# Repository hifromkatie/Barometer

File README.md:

Code and circuit diagrams for Wall mounted Barometer project.

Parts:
Arduino Uno Farnell: 2075382
MIKROE-1581 Arduino Uno click shield  Farnell:2431450
MIKROE-3216 Pressure 6 click Board (BM1386GLV Sensor) Farnell: 3013769
144LEDs per meter Neopixel strip  Farnell: 2816235
DS1307+ RTC Farnell: 2515369
32.768KHz Crystal  Farnell: 3264229
2032 coin cell  Farnell: 249877

Others: Strip board, Header pins (straight & right angle), molex connector housing & crip contacts and resistors (10K & 470).

Arduino-barometer_V0.2
Code for Arduino.

BM1386GLV_lib
library for BM1386GLV Barometric pressure sensor whhic is on the Pressure 6 Click board

RTC-mikroBUS
Schematic for RTC board, compatible with mikroBUS pin out for using with Click shield.

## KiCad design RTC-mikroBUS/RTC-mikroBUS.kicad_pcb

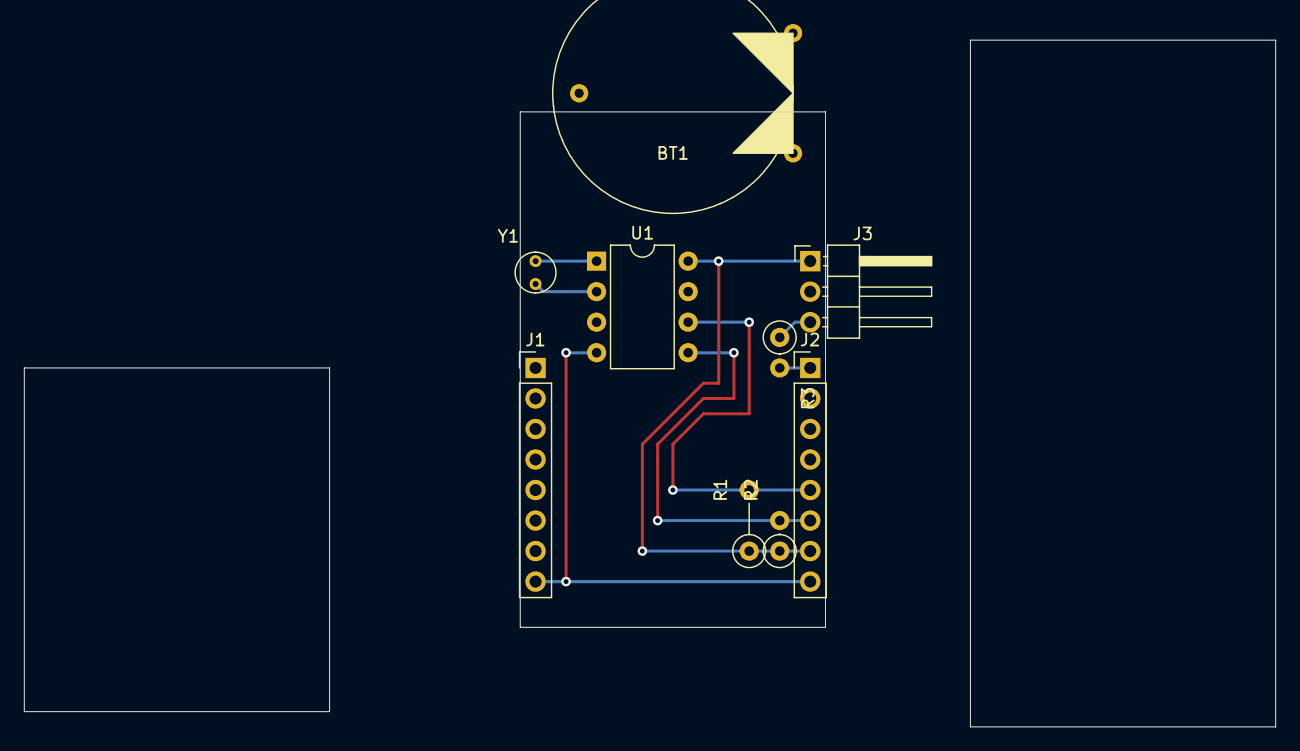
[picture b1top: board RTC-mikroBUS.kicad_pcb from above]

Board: 2 copper layers, 104.1 x 57.2 mm, 9 parts (0 on the bottom side), 9 nets.

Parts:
BT1: 3V; Varta_CR2032
J1, J2: Conn_01x08_Male; PinHeader_1x08_P2.54mm_Vertical
J3: Conn_01x03_Male; PinHeader_1x03_P2.54mm_Horizontal
R1: 10K; R_Axial_DIN0207_L6.3mm_D2.5mm_P5.08mm_Vertical
R2: 10K; R_Axial_DIN0207_L6.3mm_D2.5mm_P2.54mm_Vertical
R3: 470; R_Axial_DIN0207_L6.3mm_D2.5mm_P2.54mm_Vertical
U1: DS1307+; DIP-8_W7.62mm
Y1: 32.768KHz; Crystal_C38-LF_D3.0mm_L8.0mm_Vertical

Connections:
+5V: J2.7, J3.1, R1.1, R2.1, U1.8
GND: BT1.2, J1.8, J2.8, J3.2, U1.4
Neopixel_in: J2.1, R3.2
unnamed: BT1.1, U1.3
unnamed: J3.3, R3.1
unnamed: U1.1, Y1.1
unnamed: U1.2, Y1.2
RTC_SCL: J2.5, R1.2, U1.6
RTC_SDA: J2.6, R2.2, U1.5

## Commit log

2020-10-02 Arduino Library for BM1386GLV
2020-10-02 Delete RTC-mikroBUS.kicad_pcb
    Incorrect for stripboard
